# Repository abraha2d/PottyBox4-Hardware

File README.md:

[Schematic](Renders/schematic.pdf)

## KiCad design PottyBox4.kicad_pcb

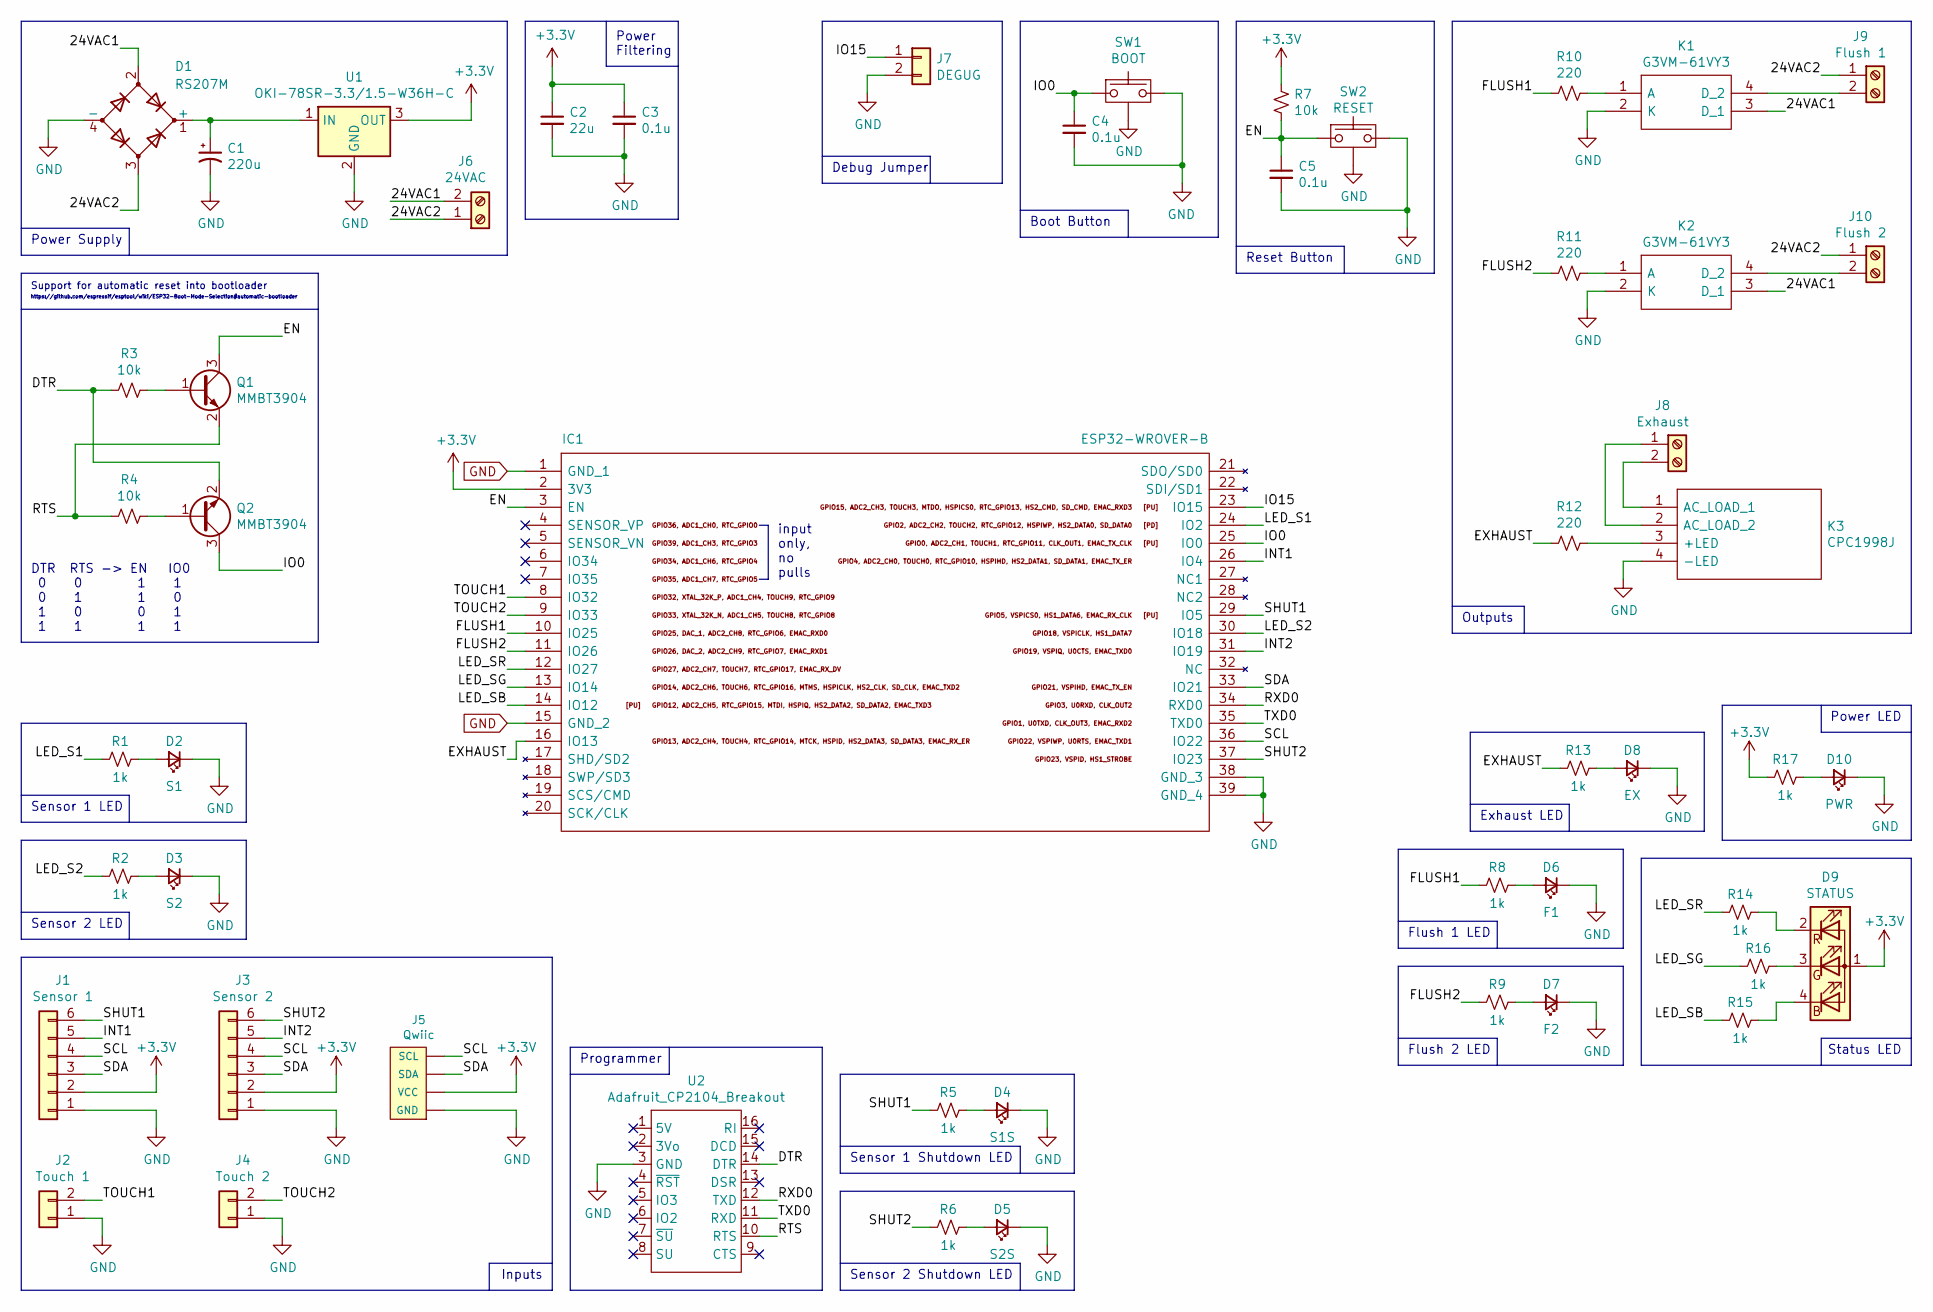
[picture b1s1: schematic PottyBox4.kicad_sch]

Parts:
C1: 220u; CP_Radial_D6.3mm_P2.50mm
C2: 22u; C_0603_1608Metric_Pad1.05x0.95mm_HandSolder
C3, C4, C5: 0.1u; C_0603_1608Metric_Pad1.05x0.95mm_HandSolder
D1: RS207M
D2: S1; LED_0603_1608Metric_Pad1.05x0.95mm_HandSolder
D3: S2; LED_0603_1608Metric_Pad1.05x0.95mm_HandSolder
D4: S1S; LED_0603_1608Metric_Pad1.05x0.95mm_HandSolder
D5: S2S; LED_0603_1608Metric_Pad1.05x0.95mm_HandSolder
D6: F1; LED_0603_1608Metric_Pad1.05x0.95mm_HandSolder
D7: F2; LED_0603_1608Metric_Pad1.05x0.95mm_HandSolder
D8: EX; LED_0603_1608Metric_Pad1.05x0.95mm_HandSolder
D9: STATUS; ASMBKTF00A306
D10: PWR; LED_0603_1608Metric_Pad1.05x0.95mm_HandSolder
IC1: ESP32-WROVER-B; ESP32WROVERIB16MB; Manufacturer_Part_Number ESP32-WROVER-B (16MB); Mouser Part Number 356-ESP32-WROB(16MB)
J1: Sensor 1; JST_SH_SM06B-SRSS-TB_1x06-1MP_P1.00mm_Horizontal
J2: Touch 1; JST_PH_S2B-PH-K_1x02_P2.00mm_Horizontal
J3: Sensor 2; JST_SH_SM06B-SRSS-TB_1x06-1MP_P1.00mm_Horizontal
J4: Touch 2; JST_PH_S2B-PH-K_1x02_P2.00mm_Horizontal
J5: Qwiic; JST_SH_SM04B-SRSS-TB_1x04-1MP_P1.00mm_Horizontal
J6: 24VAC; SCREWTERMINAL-3.5MM-2
J7: DEGUG; PinHeader_1x02_P2.54mm_Vertical
J8: Exhaust; SCREWTERMINAL-5MM-2
J9: Flush 1; SCREWTERMINAL-3.5MM-2
J10: Flush 2; SCREWTERMINAL-3.5MM-2
K1, K2: G3VM-61VY3; SOP254P700X230-4N; Manufacturer_Part_Number G3VM-61VY3(TR05); Mouser Part Number 653-G3VM-61VY3TR05
K3: CPC1998J; Manufacturer_Part_Number CPC1998J; Mouser Part Number 849-CPC1998J
Q1, Q2: MMBT3904; SOT-23
R1, R2, R5, R6, R8, R9, R13, R14, R15, R16, R17: 1k; R_0603_1608Metric_Pad1.05x0.95mm_HandSolder
R3, R4, R7: 10k; R_0603_1608Metric_Pad1.05x0.95mm_HandSolder
R10, R11, R12: 220; R_0603_1608Metric_Pad1.05x0.95mm_HandSolder
SW1: BOOT; PTS526SMG15SMTR2LFS
SW2: RESET; PTS526SMG15SMTR2LFS
U1: OKI-78SR-3.3/1.5-W36H-C; Converter_DCDC_muRata_OKI-78SR_Horizontal
U2: Adafruit_CP2104_Breakout; Adafruit_CP2104_Friend

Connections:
+3V3: C2.1, C3.1, D9.1 (A), IC1.2 (3V3), J1.2, J3.2, J5.2 (VCC), R7.1, R17.2, U1.3 (OUT)
/24VAC1: D1.2, J6.2, K1.3 (D_1), K2.3 (D_1)
/24VAC2: D1.3, J6.1, J9.1, J10.1
/DTR: Q2.2 (E), R3.2, U2.14 (DTR)
/EN: C5.1, IC1.3 (EN), Q1.3 (C), R7.2, SW2.1
/EXHAUST: IC1.16 (IO13), R12.2, R13.2
/FLUSH1: IC1.10 (IO25), R8.2, R10.2
/FLUSH2: IC1.11 (IO26), R9.2, R11.2
/INT1: IC1.26 (IO4), J1.5
/INT2: IC1.31 (IO19), J3.5
/IO0: C4.1, IC1.25 (IO0), Q2.3 (C), SW1.1
/IO15: IC1.23 (IO15), J7.1
/LED_S1: IC1.24 (IO2), R1.2
/LED_S2: IC1.30 (IO18), R2.2
/LED_SB: IC1.14 (IO12), R15.2
/LED_SG: IC1.13 (IO14), R16.2
/LED_SR: IC1.12 (IO27), R14.2
/RTS: Q1.2 (E), R4.2, U2.10 (RTS)
/RXD0: IC1.34 (RXD0), U2.12 (TXD)
/SCL: IC1.36 (IO22), J1.4, J3.4, J5.4 (SCL)
/SDA: IC1.33 (IO21), J1.3, J3.3, J5.3 (SDA)
/SHUT1: IC1.29 (IO5), J1.6, R5.2
/SHUT2: IC1.37 (IO23), J3.6, R6.2
/TOUCH1: IC1.8 (IO32), J2.2
/TOUCH2: IC1.9 (IO33), J4.2
/TXD0: IC1.35 (TXD0), U2.11 (RXD)
GND: C1.2, C2.2, C3.2, C4.2, C5.2, D1.4 (-), D2.1 (K), D3.1 (K), D4.1 (K), D5.1 (K), D6.1 (K), D7.1 (K), D8.1 (K), D10.1 (K), IC1.1 (GND_1), IC1.15 (GND_2), IC1.38 (GND_3), IC1.39 (GND_4), J1.1, J2.1, J3.1, J4.1, J5.1 (GND), J7.2, K1.2 (K), K2.2 (K), K3.4 (-LED), SW1.2, SW1.SH (Shield), SW2.2, SW2.SH (Shield), U1.2 (GND), U2.3 (GND)
unnamed: C1.1, D1.1 (+), U1.1 (IN)
unnamed: D2.2 (A), R1.1
unnamed: D3.2 (A), R2.1
unnamed: D4.2 (A), R5.1
unnamed: D5.2 (A), R6.1
unnamed: D6.2 (A), R8.1
unnamed: D7.2 (A), R9.1
unnamed: D8.2 (A), R13.1
unnamed: D9.2 (RK), R14.1
unnamed: D9.3 (GK), R16.1
unnamed: D9.4 (BK), R15.1
unnamed: D10.2 (A), R17.1
unnamed: J8.1, K3.2 (AC_LOAD_2)
unnamed: J8.2, K3.1 (AC_LOAD_1)
unnamed: J9.2, K1.4 (D_2)
unnamed: J10.2, K2.4 (D_2)
unnamed: K1.1 (A), R10.1
unnamed: K2.1 (A), R11.1
unnamed: K3.3 (+LED), R12.1
unnamed: Q1.1 (B), R3.1
unnamed: Q2.1 (B), R4.1

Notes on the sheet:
Power Supply
Support for automatic reset into bootloader
https://github.com/espressif/esptool/wiki/ESP32-Boot-Mode-Selection#automatic-bootloader
DTR RTS -> EN IO0 0 0 1 1 0 1 1 0 1 0 0 1 1 1 1 1
Sensor 1 LED
Sensor 2 LED
Inputs
Programmer
Power Filtering
input only, no pulls
Debug Jumper
Sensor 1 Shutdown LED
Sensor 2 Shutdown LED
Boot Button
Reset Button
Flush 1 LED
Flush 2 LED
Outputs
Exhaust LED
Power LED
Status LED

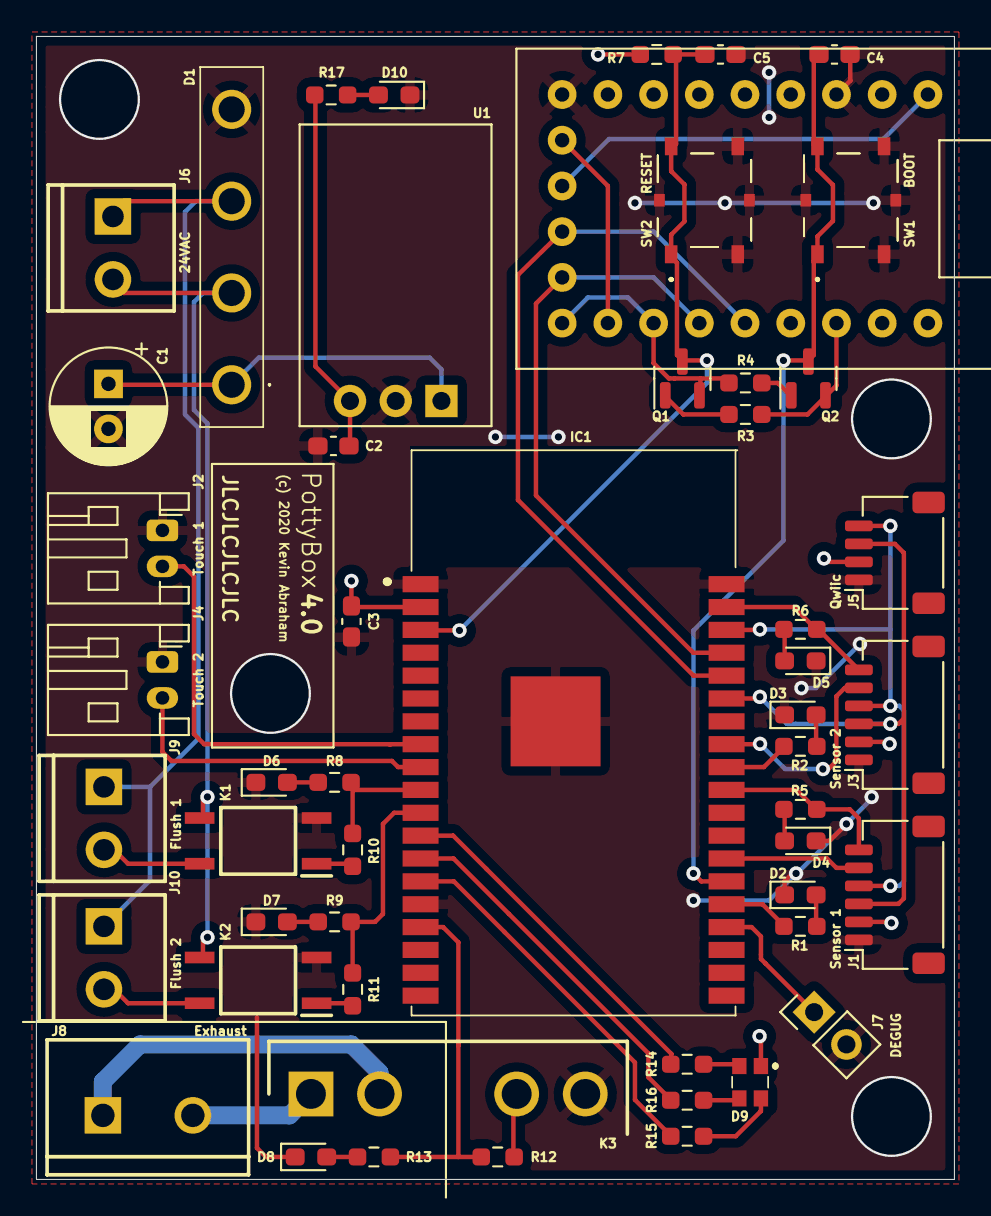
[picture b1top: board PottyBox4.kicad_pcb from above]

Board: 2 copper layers, 51.0 x 63.5 mm, 52 parts (0 on the bottom side), 48 nets.

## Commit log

2019-12-15 Add KiCad project
2019-12-15 Add teensy symbols from XenGi/teensy_library, footprints from XenGi/teensy.pretty
2020-01-05 Add Adafruit CP2104 Friend symbol. Something's wrong with the Symbol Editor, so it's not fully saved...
2020-01-05 Found issue already reported, workaround seems to work for now. https://gitlab.com/kicad/code/kicad/issues/3665
2020-01-06 Add symbol/footprint/3D for ESP32-WROVER-B
2020-01-07 Add symbol/footprint/3D for MMBT3904
2020-01-09 Add lots of parts and stuff...
2020-01-09 Get power, reset/boot buttons, led, input terminals, etc on schematic
2020-01-09 Put outputs on schematic
2020-01-12 Update WROVER symbol with GPIO info, clean up schematic
2020-01-12 Add boot strapping pin details to symbol, add debug output configuration jumper
2020-01-14 Add LEDs
2020-02-17 Finish up schematic, start layout work
2020-02-17 Wire up sensor ports, LEDs, and Qwiic port to ESP32
2020-02-18 ERC/DRC down to a minimum
2020-02-18 Layout complete, clean ERC/DRC
2020-02-20 Optimize layout, cleanup
2020-02-20 Final touches
2020-03-23 Final review and modifications (thanks @tarasjg)
2021-10-30 Update to work with KiCad pre-6
2021-10-30 Add schematic link, title block data
2021-12-21 Convert to newer version of kicad_sch

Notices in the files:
PottyBox4.kicad_pcb:
(c) 2020 Kevin Abraham
